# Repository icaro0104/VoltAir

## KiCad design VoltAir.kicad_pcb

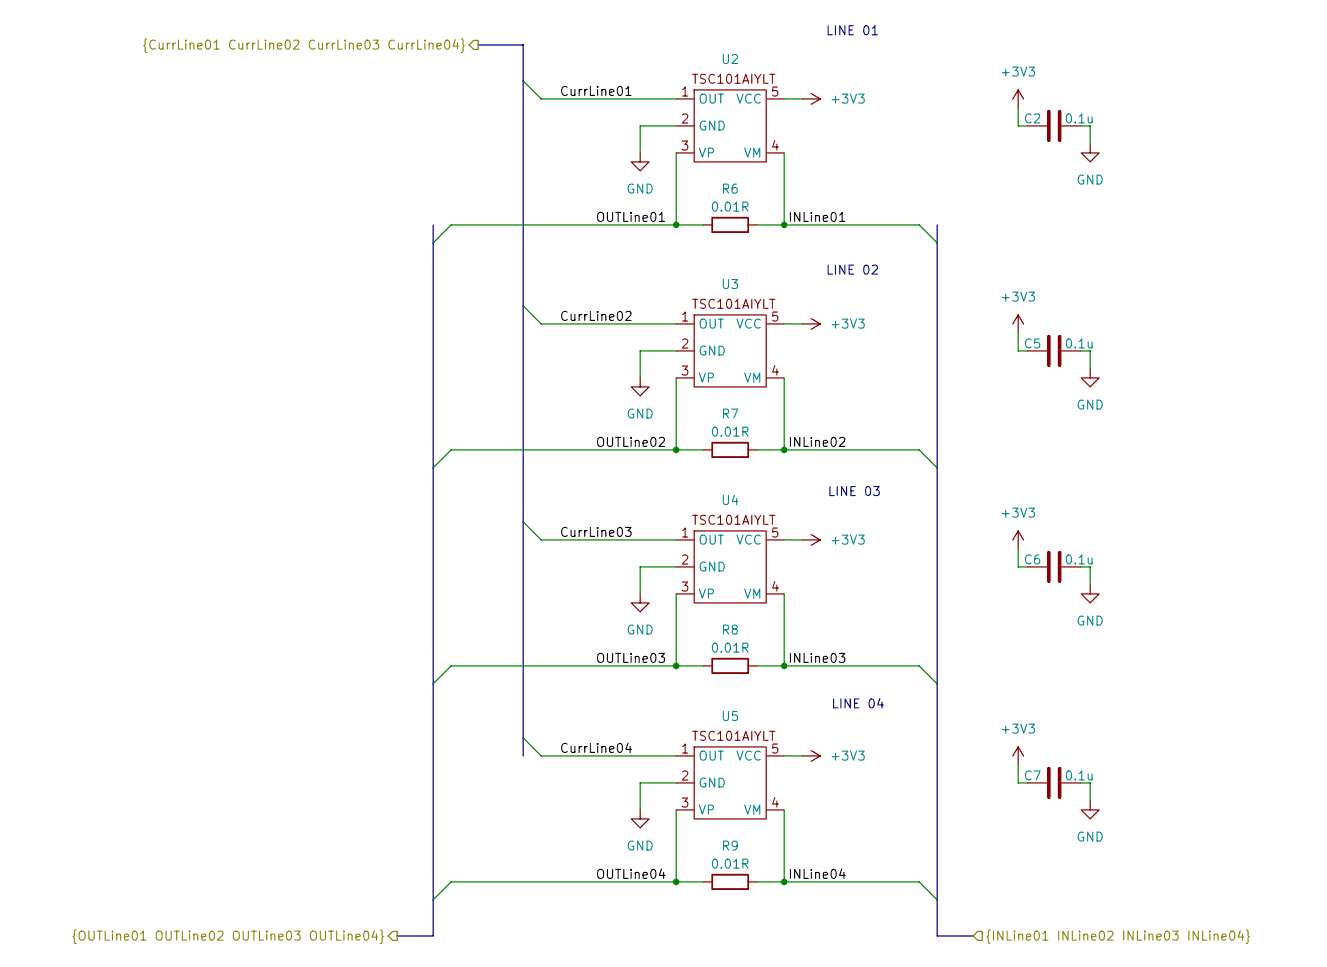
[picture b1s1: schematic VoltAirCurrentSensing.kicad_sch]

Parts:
C2, C5, C6, C7: 0.1u; C_0603_1608Metric
R6, R7, R8, R9: 0.01R; R_Shunt_Vishay_WSR2_WSR3
U2, U3, U4, U5: SOT-23-5_HandSoldering

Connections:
+3V3: C2.2, C5.2, C6.2, C7.2, U2.5 (VCC), U3.5 (VCC), U4.5 (VCC), U5.5 (VCC); also elsewhere on the board
/CurrentSensing/CurrLine01: U2.1 (OUT); also elsewhere on the board
/CurrentSensing/CurrLine02: U3.1 (OUT); also elsewhere on the board
/CurrentSensing/CurrLine03: U4.1 (OUT); also elsewhere on the board
/CurrentSensing/CurrLine04: U5.1 (OUT); also elsewhere on the board
/CurrentSensing/INLine01: R6.2, U2.4 (VM); also elsewhere on the board
/CurrentSensing/INLine02: R7.2, U3.4 (VM); also elsewhere on the board
/CurrentSensing/INLine03: R8.2, U4.4 (VM); also elsewhere on the board
/CurrentSensing/INLine04: R9.2, U5.4 (VM); also elsewhere on the board
/CurrentSensing/OUTLine01: R6.1, U2.3 (VP); also elsewhere on the board
/CurrentSensing/OUTLine02: R7.1, U3.3 (VP); also elsewhere on the board
/CurrentSensing/OUTLine03: R8.1, U4.3 (VP); also elsewhere on the board
/CurrentSensing/OUTLine04: R9.1, U5.3 (VP); also elsewhere on the board
GND: C2.1, C5.1, C6.1, C7.1, U2.2 (GND), U3.2 (GND), U4.2 (GND), U5.2 (GND); also elsewhere on the board

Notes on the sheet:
LINE 03
LINE 02
LINE 04
LINE 01

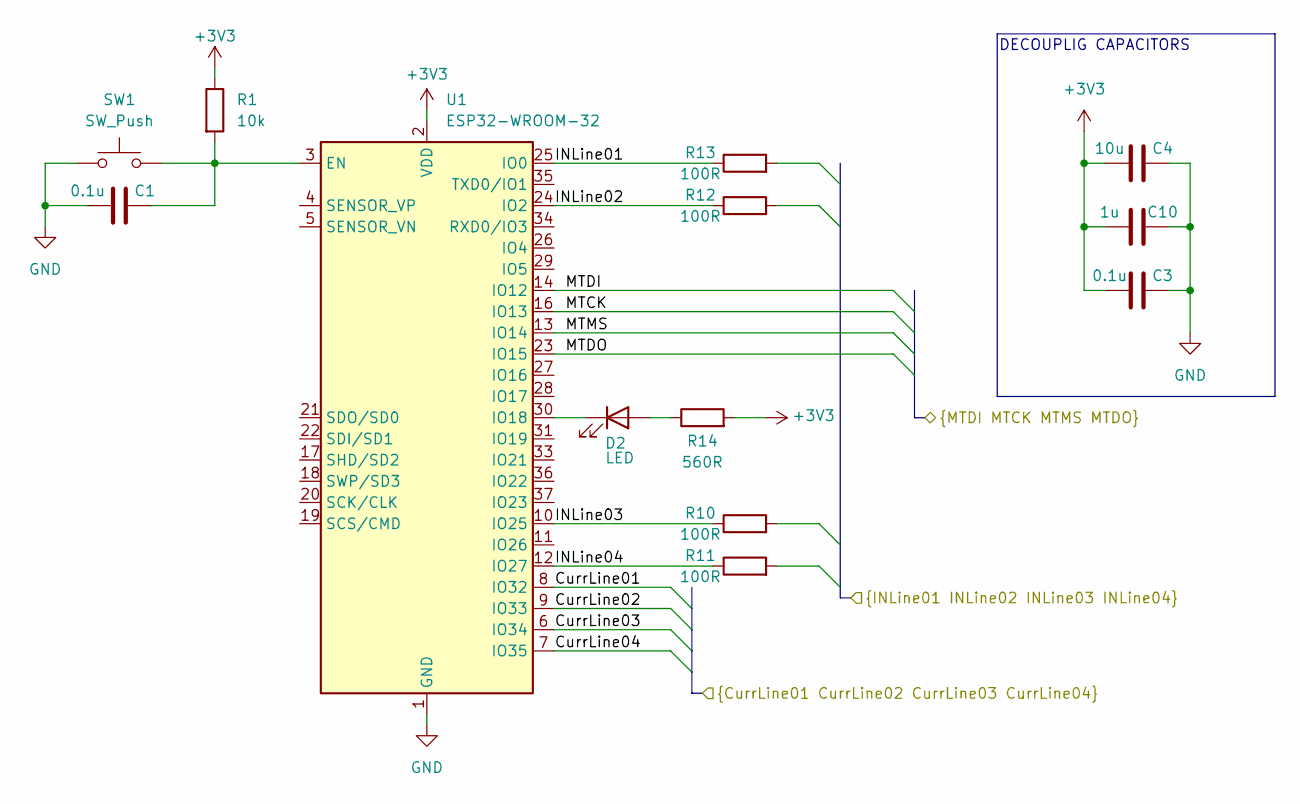
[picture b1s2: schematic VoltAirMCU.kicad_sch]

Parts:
C1, C3: 0.1u; C_0603_1608Metric
C4: 10u; CP_EIA-3216-18_Kemet-A_Pad1.58x1.35mm_HandSolder
C10: 1u; C_0603_1608Metric
D2: LED; LED_0603_1608Metric
R1: 10k; R_0603_1608Metric
R10, R11, R12, R13: 100R; R_0603_1608Metric
R14: 560R; R_0603_1608Metric
SW1: SW_Push; SW_PUSH_1P1T_6x3.5mm_H5.0_APEM_MJTP1250
U1: ESP32-WROOM-32

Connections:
+3V3: C3.1, C4.1, C10.1, R1.1, R14.2, U1.2 (VDD); also elsewhere on the board
/CurrentSensing/CurrLine01: U1.8 (IO32); also elsewhere on the board
/CurrentSensing/CurrLine02: U1.9 (IO33); also elsewhere on the board
/CurrentSensing/CurrLine03: U1.6 (IO34); also elsewhere on the board
/CurrentSensing/CurrLine04: U1.7 (IO35); also elsewhere on the board
/CurrentSensing/INLine01: R13.1, U1.25 (IO0); also elsewhere on the board
/CurrentSensing/INLine02: R12.1, U1.24 (IO2); also elsewhere on the board
/CurrentSensing/INLine03: R10.1, U1.10 (IO25); also elsewhere on the board
/CurrentSensing/INLine04: R11.1, U1.12 (IO27); also elsewhere on the board
/JTAG/MTCK: U1.16 (IO13); also elsewhere on the board
/JTAG/MTDI: U1.14 (IO12); also elsewhere on the board
/JTAG/MTDO: U1.23 (IO15); also elsewhere on the board
/JTAG/MTMS: U1.13 (IO14); also elsewhere on the board
GND: C1.1, C3.2, C4.2, C10.2, SW1.1, U1.1 (GND), U1.15 (GND), U1.38 (GND), U1.39 (GND); also elsewhere on the board
unnamed: D2.2 (A), R14.1
unnamed: D2.1 (K), U1.30 (IO18)
unnamed: C1.2, R1.2, SW1.2, U1.3 (EN)

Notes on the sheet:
DECOUPLIG CAPACITORS

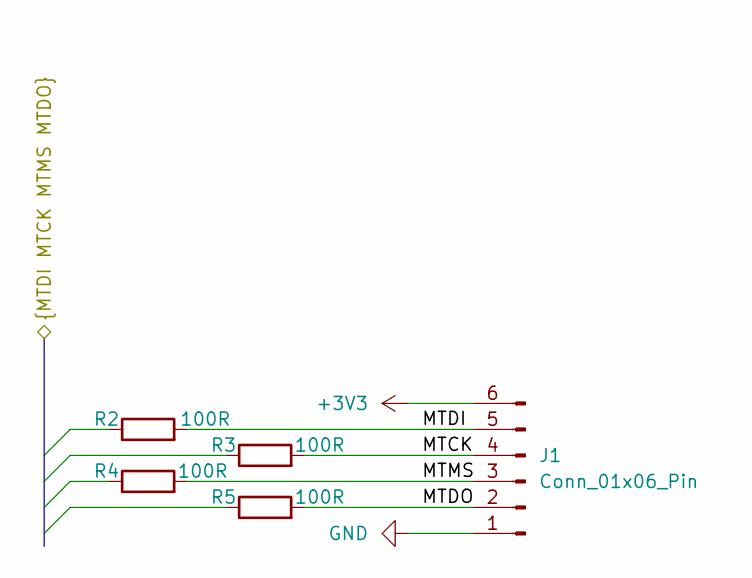
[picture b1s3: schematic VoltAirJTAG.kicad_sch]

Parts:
J1: Conn_01x06_Pin; PinHeader_1x06_P1.00mm_Vertical
R2, R3, R4, R5: 100R; R_0603_1608Metric

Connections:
+3V3: J1.6; also elsewhere on the board
/JTAG/MTCK: J1.4, R3.2; also elsewhere on the board
/JTAG/MTDI: J1.5, R2.2; also elsewhere on the board
/JTAG/MTDO: J1.2, R5.2; also elsewhere on the board
/JTAG/MTMS: J1.3, R4.2; also elsewhere on the board
GND: J1.1; also elsewhere on the board

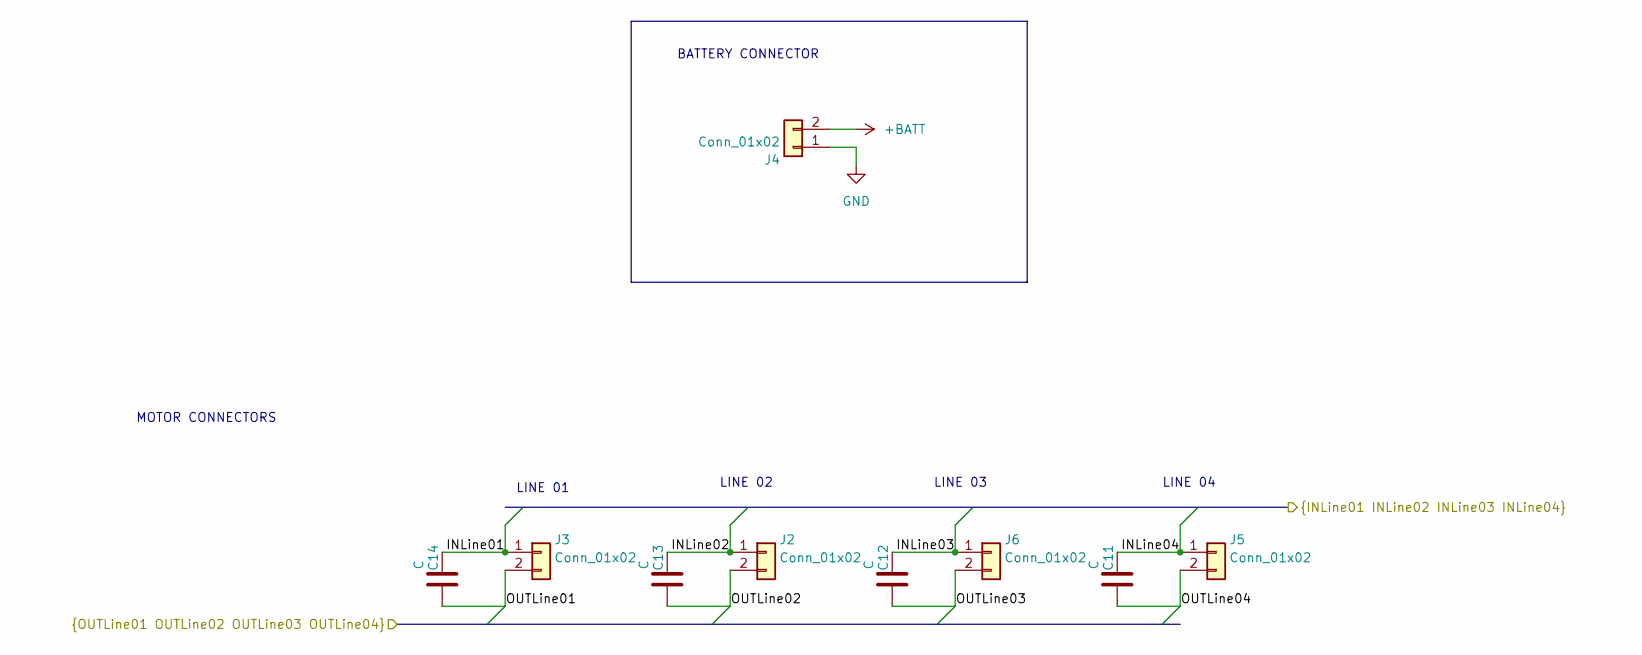
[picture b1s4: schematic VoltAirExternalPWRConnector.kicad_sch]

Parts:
C11, C12, C13, C14: C; CP_Radial_D8.0mm_P5.00mm
J2, J3, J5, J6: Conn_01x02; TestPoint_2Pads_Pitch5.08mm_Drill1.3mm
J4: Conn_01x02; Molex_PicoBlade_53047-0210_1x02_P1.25mm_Vertical

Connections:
+BATT: J4.2; also elsewhere on the board
/CurrentSensing/INLine01: C14.1, J3.1; also elsewhere on the board
/CurrentSensing/INLine02: C13.1, J2.1; also elsewhere on the board
/CurrentSensing/INLine03: C12.1, J6.1; also elsewhere on the board
/CurrentSensing/INLine04: C11.1, J5.1; also elsewhere on the board
/CurrentSensing/OUTLine01: C14.2, J3.2; also elsewhere on the board
/CurrentSensing/OUTLine02: C13.2, J2.2; also elsewhere on the board
/CurrentSensing/OUTLine03: C12.2, J6.2; also elsewhere on the board
/CurrentSensing/OUTLine04: C11.2, J5.2; also elsewhere on the board
GND: J4.1; also elsewhere on the board

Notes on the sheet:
MOTOR CONNECTORS
LINE 03
LINE 04
LINE 01
LINE 02
BATTERY CONNECTOR

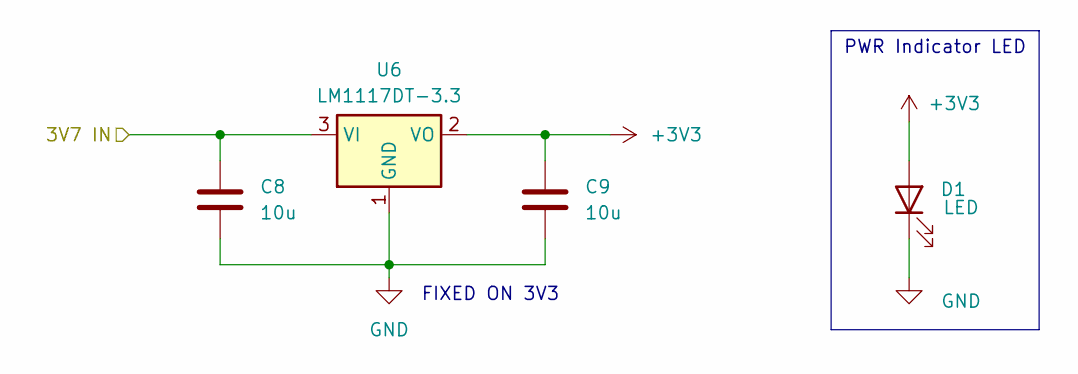
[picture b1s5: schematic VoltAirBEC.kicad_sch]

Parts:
C8, C9: 10u; CP_EIA-3216-18_Kemet-A_Pad1.58x1.35mm_HandSolder
D1: LED; LED_0603_1608Metric
U6: LM1117DT-3.3; TO-252-3_TabPin2

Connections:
+3V3: C9.1, D1.2 (A), U6.2 (VO); also elsewhere on the board
+BATT: C8.1, U6.3 (VI); also elsewhere on the board
GND: C8.2, C9.2, D1.1 (K), U6.1 (GND); also elsewhere on the board

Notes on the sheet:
PWR Indicator LED
FIXED ON 3V3

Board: 2 copper layers, 43 parts (0 on the bottom side), 22 nets, no tracks yet.

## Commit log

2025-01-13 Late initial commit
    Schematic is finished.
2025-01-13 Minor footprint ajustment
2025-01-13 initial layout
